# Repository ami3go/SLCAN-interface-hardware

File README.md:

# SLCAN-interface-hardware
 Harware adapter for SLCAN interface based on MCP2515 and Arduino micro

 Those 3 project are connected: 
 - https://github.com/ami3go/SLCAN-python-examples
 - https://github.com/ami3go/SLCAN-interface-hardware
 - https://github.com/ami3go/SLCAN-interface-firmware

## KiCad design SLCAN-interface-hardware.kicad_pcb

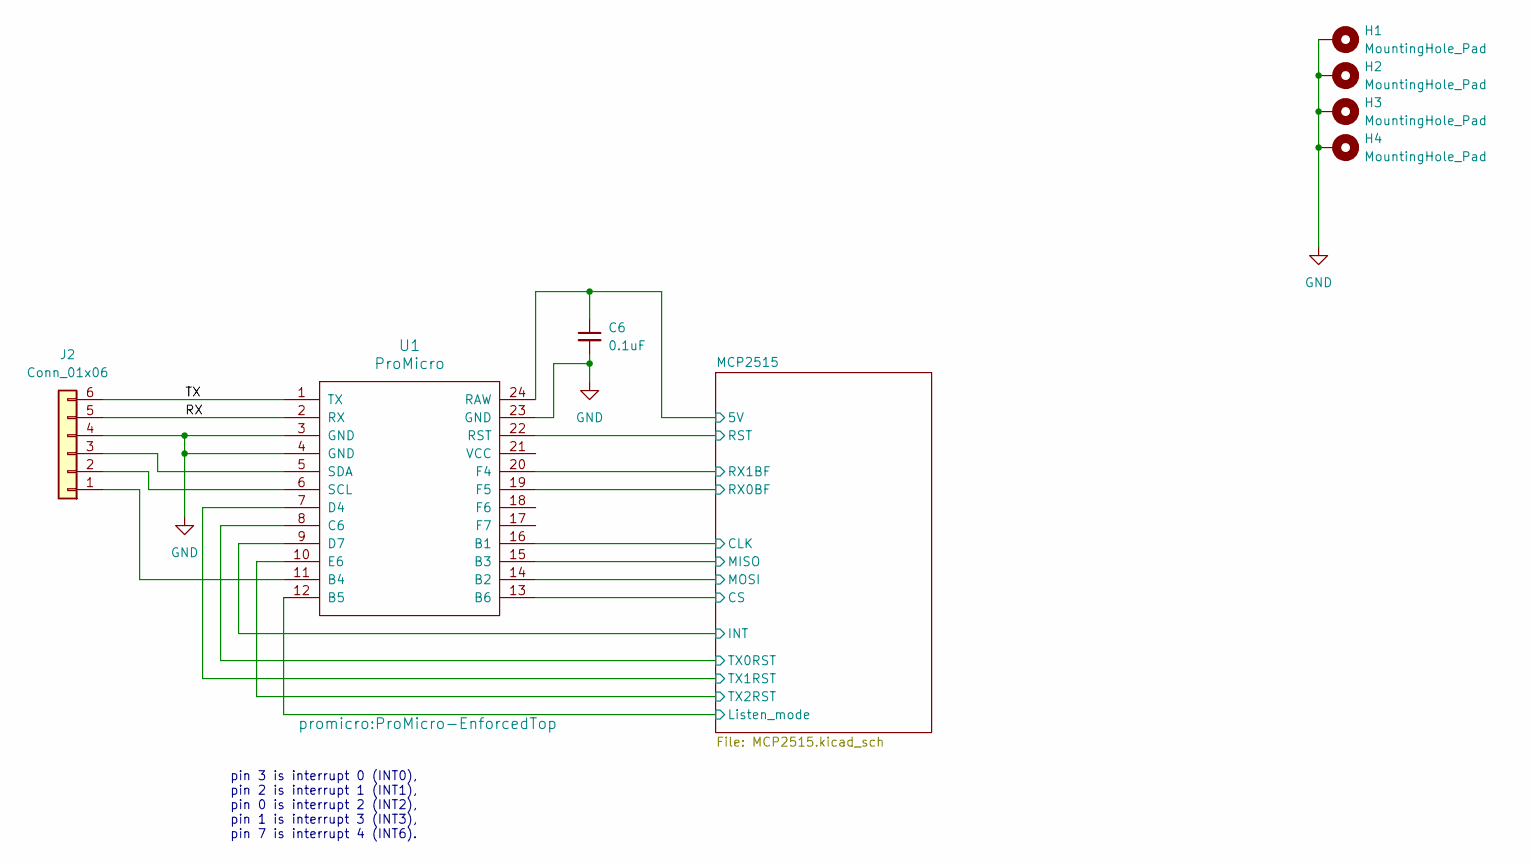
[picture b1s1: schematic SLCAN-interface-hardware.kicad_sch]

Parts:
C6: 100nF_0603_16V; C_0603; Part Number 0603YC104KAT2A; JLCPCB ID C14663
H1, H2, H3, H4: MountingHole_Pad; MountingHole_3.5mm_Pad_Via
J2: Conn_01x06; Pins_1x06_2.54mm_TH_SWD; Part Number 1-0601FBV0T
U1: ProMicro; ProMicro-EnforcedTop

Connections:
/MCP2515/5V: C6.1, U1.24 (RAW); also elsewhere on the board
/MCP2515/CLK: U1.16 (B1); also elsewhere on the board
/MCP2515/CS: U1.13 (B6); also elsewhere on the board
/MCP2515/INT: U1.9 (D7); also elsewhere on the board
/MCP2515/Listen_mode: U1.12 (B5); also elsewhere on the board
/MCP2515/MISO: U1.15 (B3); also elsewhere on the board
/MCP2515/MOSI: U1.14 (B2); also elsewhere on the board
/MCP2515/RST: U1.22 (RST); also elsewhere on the board
/MCP2515/RX0BF: U1.19 (F5); also elsewhere on the board
/MCP2515/RX1BF: U1.20 (F4); also elsewhere on the board
/MCP2515/TX0RST: U1.8 (C6); also elsewhere on the board
/MCP2515/TX1RST: U1.7 (D4); also elsewhere on the board
/MCP2515/TX2RST: U1.10 (E6); also elsewhere on the board
/RX: J2.5, U1.2 (RX)
/TX: J2.6, U1.1 (TX)
GND: C6.2, H1.1, H2.1, H3.1, H4.1, J2.4, U1.3 (GND), U1.4 (GND), U1.23 (GND); also elsewhere on the board
unnamed: J2.1, U1.11 (B4)
unnamed: J2.2, U1.6 (SCL)
unnamed: J2.3, U1.5 (SDA)

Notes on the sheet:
pin 3 is interrupt 0 (INT0), pin 2 is interrupt 1 (INT1), pin 0 is interrupt 2 (INT2), pin 1 is interrupt 3 (INT3), pin 7 is interrupt 4 (INT6).

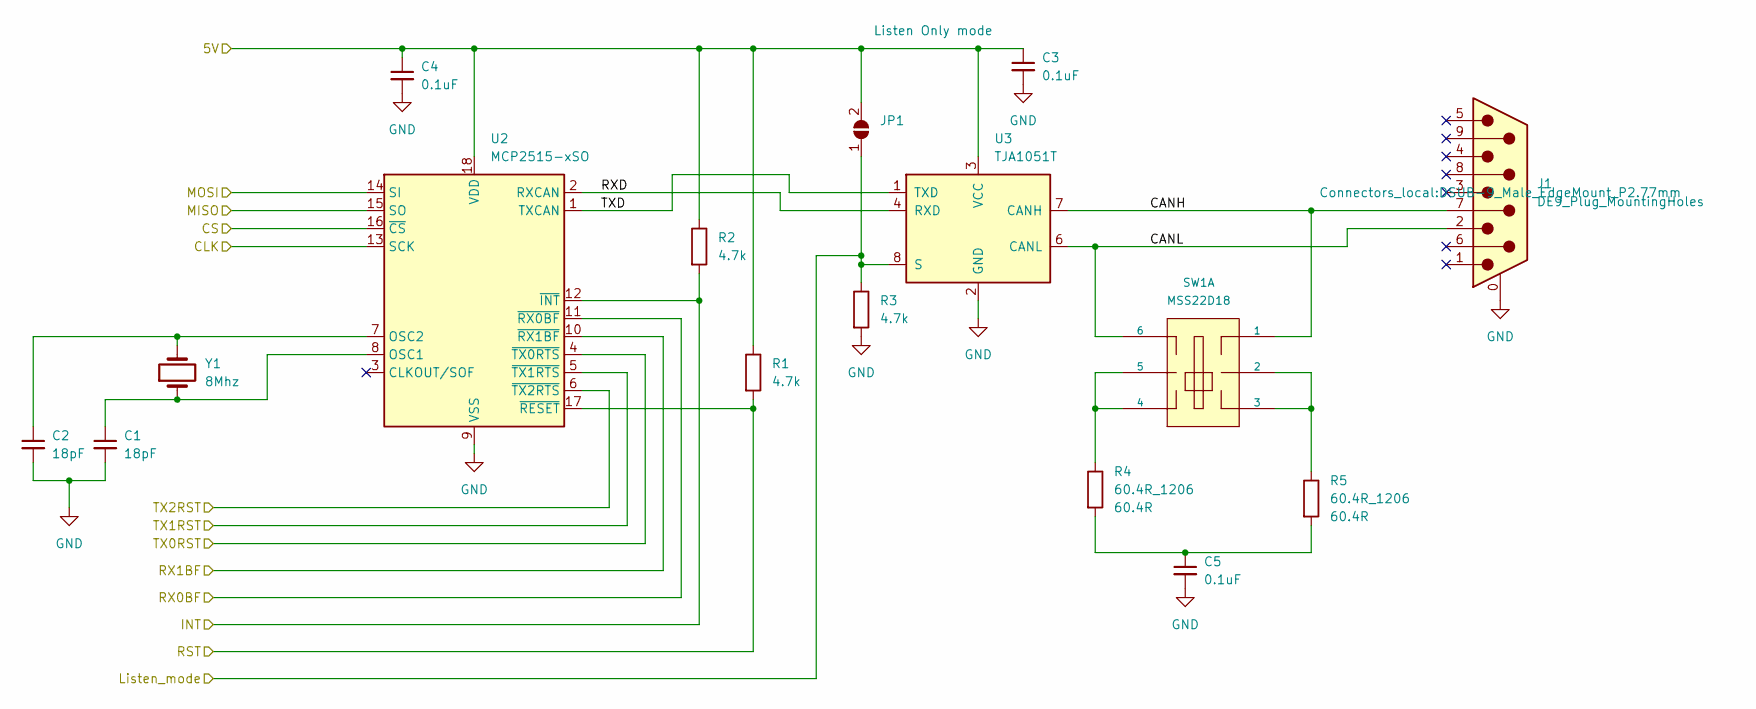
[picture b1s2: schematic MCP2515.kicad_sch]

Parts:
C1, C2: 18pF_0603_50V; C_0603; Part Number C0603C180J5GACTU; JLCPCB ID C1647
C3, C4, C5: 100nF_0603_16V; C_0603; Part Number 0603YC104KAT2A; JLCPCB ID C14663
J1: DE9_Plug_MountingHoles; DSUB-9_Male_EdgeMount_P2.77mm
JP1: SolderJumper_2_Open; SolderJumper-2_P1.3mm_Open_RoundedPad1.0x1.5mm
R1, R2, R3: 4.7k_0603; R_0603; Part Number RC0603FR-074K7L; JLCPCB ID C23162
R4, R5: 60.4R_1206; R_1206_3216Metric; Part Number CR1206-FX-60R4ELF
SW1: MSS22D18; Part Number MSS22D18
U2: MCP2515-xSO; SOIC-18W_7.5x11.6mm_P1.27mm
U3: TJA1051T; SOIC-8_3.9x4.9mm_P1.27mm
Y1: 8Mhz; Crystal_HC49-4H_Vertical

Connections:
/MCP2515/5V: C3.1, C4.1, JP1.2 (B), R1.1, R2.1, U2.18 (VDD), U3.3 (VCC); also elsewhere on the board
/MCP2515/CANH: J1.7, SW1.1, U3.7 (CANH)
/MCP2515/CANL: J1.2, SW1.6, U3.6 (CANL)
/MCP2515/CLK: U2.13 (SCK); also elsewhere on the board
/MCP2515/CS: U2.16 (~CS); also elsewhere on the board
/MCP2515/INT: R2.2, U2.12 (~INT); also elsewhere on the board
/MCP2515/Listen_mode: JP1.1 (A), R3.1, U3.8 (S); also elsewhere on the board
/MCP2515/MISO: U2.15 (SO); also elsewhere on the board
/MCP2515/MOSI: U2.14 (SI); also elsewhere on the board
/MCP2515/RST: R1.2, U2.17 (~RESET); also elsewhere on the board
/MCP2515/RX0BF: U2.11 (~RX0BF); also elsewhere on the board
/MCP2515/RX1BF: U2.10 (~RX1BF); also elsewhere on the board
/MCP2515/RXD: U2.2 (RXCAN), U3.4 (RXD)
/MCP2515/TX0RST: U2.4 (~TX0RTS); also elsewhere on the board
/MCP2515/TX1RST: U2.5 (~TX1RTS); also elsewhere on the board
/MCP2515/TX2RST: U2.6 (~TX2RTS); also elsewhere on the board
/MCP2515/TXD: U2.1 (TXCAN), U3.1 (TXD)
GND: C1.2, C2.2, C3.2, C4.2, C5.2, J1.0 (PAD), R3.2, U2.9 (VSS), U3.2 (GND); also elsewhere on the board
unnamed: C5.1, R4.2, R5.2
unnamed: R4.1, SW1.4, SW1.5
unnamed: R5.1, SW1.2, SW1.3
unnamed: C1.1, U2.8 (OSC1), Y1.1
unnamed: C2.1, U2.7 (OSC2), Y1.2

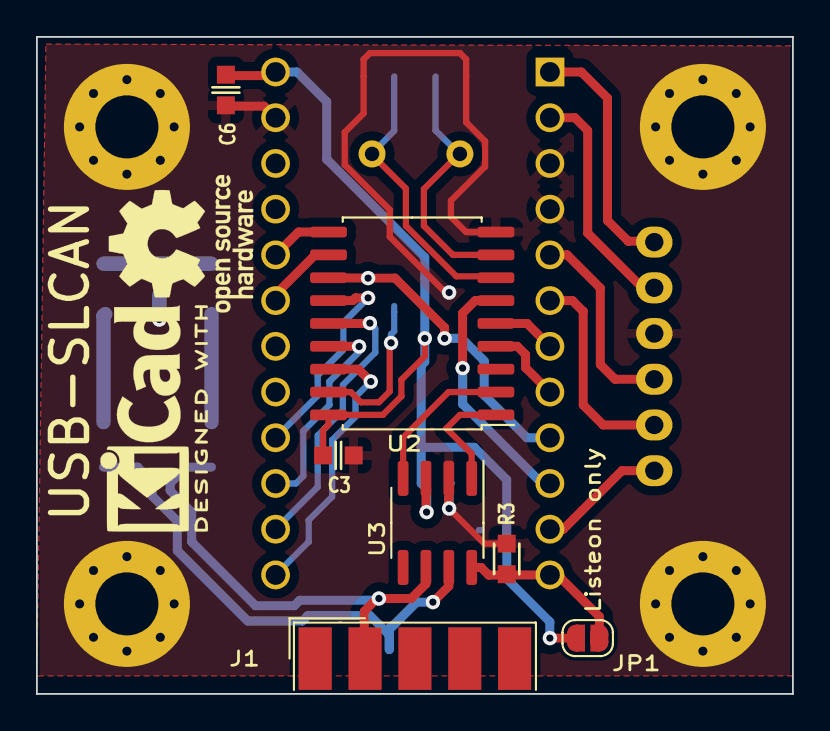
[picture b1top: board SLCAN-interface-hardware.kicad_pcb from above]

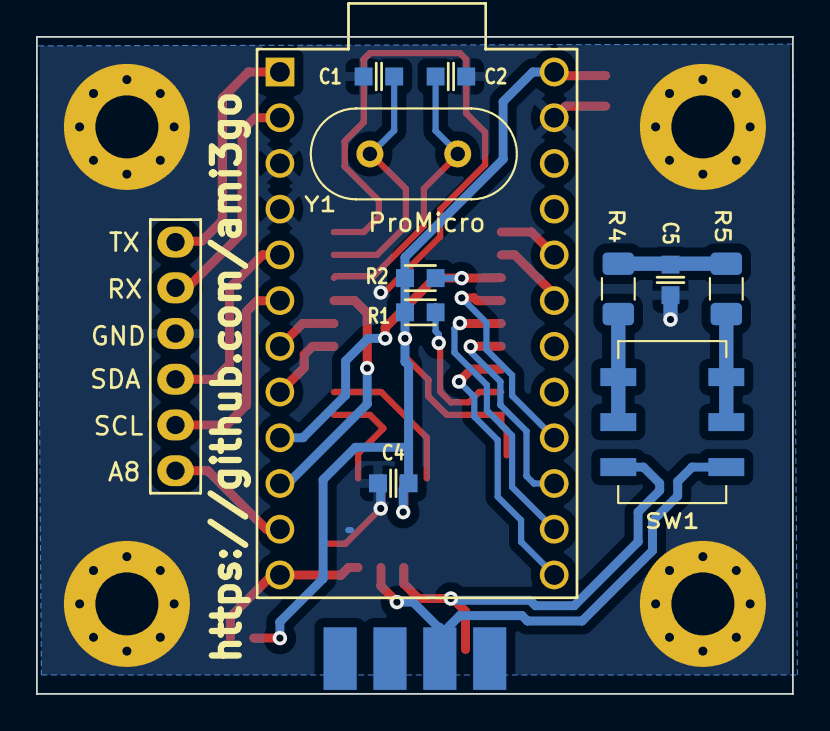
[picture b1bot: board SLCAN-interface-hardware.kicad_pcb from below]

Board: 2 copper layers, 42.0 x 36.5 mm, 23 parts (12 on the bottom side), 28 nets.

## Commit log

2024-05-03 add images
2024-05-03 images update
2024-05-03 Add step model
2025-08-05 Start working on enclosure
